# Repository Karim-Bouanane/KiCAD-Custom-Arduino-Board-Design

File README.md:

# **KiCAD-Custom-Arduino-Board-Design**

## **What is expected from this project ?**

This project goal was to touch the fundamental basis, from design to fabrication process of the PCB board. That's why I decided to build my own custom Arduino Nano Board from scratch using the KiCAD software which is totally free and offers many great tools. 
However due to my lack of some knowledge in electricity and the pressed time, I decided to give up some enhancements and postpone them when I finish my studies.

## **Subsystems**

## Voltage Regulator

I used the famous AMS117-3.3 voltage regulator known by its low cost and its availibity in the market. This IC can support a wide range of input voltage (4.0 up to 12V) and can deliver 3.3V with 1A output current capability. Its maximum drop out voltage can reach 1.3V.

The placement and values of capacitors were used from the datasheet. In addition I've added the Power On LED to lighten up when power is available.

## Oscillator

Ceramic and crystal oscillators are the main clock source and each has many types. The choice was mainly based on the frequency accuracy which provide each of them. Crystal Oscillator provides much more accurate output, of about 30 to 50ppm (part per million), than the Ceramic resonator which has +-1% of accuracy. The one I used for the atmega328 has a tolerance of 20ppm with a frequency of 16Mhz. The below circuit schema was made following the indication of datasheet.

## RESET pin

The reset pin is active low, so it needs a pull up resistor and I've added a switch button to put microcontroller in reset state manually in order to program it.

## Connectors

They are the interface we use to access the pins of the ATMEGA328P. The through whole connectors I used are the same as the ones on the Arduino Nano, they come ina single vertical row of 15 connectors with a size of 2.5mm. 

## UART pins

In order to observe any ongoing communication in the UART pins (RX, TX), I put two LEDS with a high resistance value.

## ICSP Interface

ICSP stands for In Circuit Serial Programming, which represents one of the several methods available for programming Arduino boards. Ordinarily, an Arduino bootloader program is used to program an Arduino board, but if the bootloader is missing or damaged, ICSP can be used instead. The ICSP uses pins of the SPI interface which are MISO, MOSI, SCK. 

## ATMEGA328P

### I2C pull up resistors

I2C peripheral uses open-drain pins so all they can do is assert the lines low, and pullup resistors pull the line high when it is not driven low. Also the pull-ups can be different values for different I2C speeds so they have to be external for that flexibility. I choosed the same value as like the ones used in Arduino Nano.

### AVCC low pass filter

So as to gain more accuracy in analogic operations, the data sheet for the ATMEGA328 chip says that AVCC should be connected externally to VCC via a low-pass filter if low noise is important to our application.

### User LED

This LED is attached to pin 13 and is built in most of the boards. It's not used by microcontroller but is there for the user to control. 

## **Whole Schemtaic**

## **3D front view**

## **3D back view**

## **References :**

Very informative references that I used:

- The official open source schematic published by arduino.cc

- This amazing website which thought me almost everything about every subsystem used in arduino with great explanation : https://rheingoldheavy.com/arduino-from-scratch-series/

- This is a concise playlist for using KiCAD software made by the incredible teacher Shawn Hymel which has a fun and attractive style of teaching : https://www.youtube.com/watch?v=vaCVh2SAZY4&list=PL3bNyZYHcRSUhUXUt51W6nKvxx2ORvUQB

- My selection of components was based on this list of parts that offer JLCPCB manufacturer:  https://jlcpcb.com/parts

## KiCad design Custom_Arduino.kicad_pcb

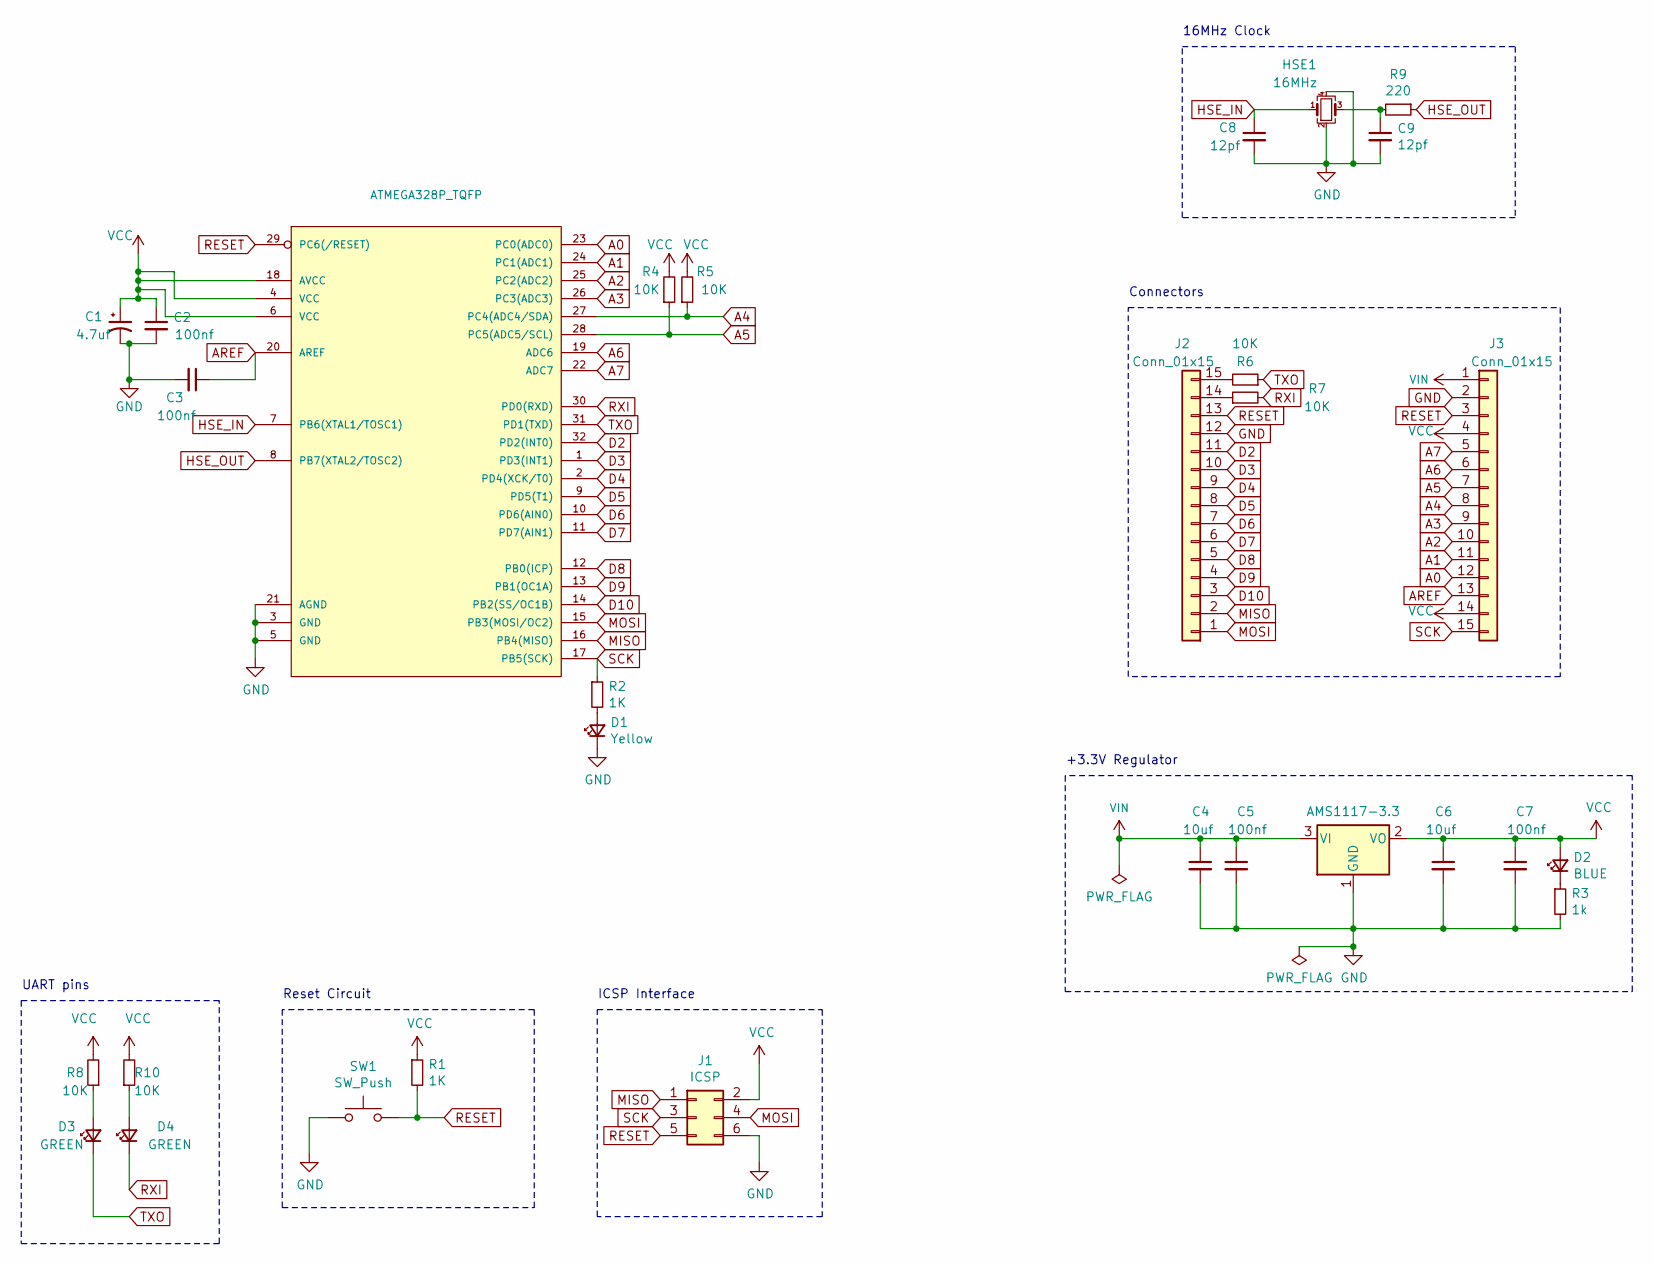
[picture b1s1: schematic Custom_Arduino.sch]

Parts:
C1: 4.7uf; C_0402_1005Metric
C2, C3, C5, C7: 100nf; C_0402_1005Metric
C4, C6: 10uf; C_0402_1005Metric
C8, C9: 12pf; C_0402_1005Metric
D1: Yellow; LED_0603_1608Metric
D2: BLUE; LED_0603_1608Metric
D3, D4: GREEN; LED_0603_1608Metric
HSE1: 16MHz; Crystal_SMD_3225-4Pin_3.2x2.5mm
J1: ICSP; PinHeader_2x03_P2.54mm_Vertical
J2, J3: Conn_01x15; PinHeader_1x15_P2.54mm_Vertical
R1, R2: 1K; R_0603_1608Metric
R3: 1k; R_0603_1608Metric
R4, R5, R6, R7, R8, R10: 10K; R_0603_1608Metric
R9: 220; R_0603_1608Metric
SW1: SW_Push; TACTILE_SWITCH_SMD_5.2MM
U1: ATMEGA328P_TQFP; TQFP32-08
U2: AMS1117-3.3; SOT-223-3_TabPin2

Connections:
A0: J3.12, U1.23 (PC0(ADC0))
A1: J3.11, U1.24 (PC1(ADC1))
A2: J3.10, U1.25 (PC2(ADC2))
A3: J3.9, U1.26 (PC3(ADC3))
A4: J3.8, R5.1, U1.27 (PC4(ADC4/SDA))
A5: J3.7, R4.1, U1.28 (PC5(ADC5/SCL))
A6: J3.6, U1.19 (ADC6)
A7: J3.5, U1.22 (ADC7)
AREF: C3.1, J3.13, U1.20 (AREF)
D2: J2.11, U1.32 (PD2(INT0))
D3: J2.10, U1.1 (PD3(INT1))
D4: J2.9, U1.2 (PD4(XCK/T0))
D5: J2.8, U1.9 (PD5(T1))
D6: J2.7, U1.10 (PD6(AIN0))
D7: J2.6, U1.11 (PD7(AIN1))
D8: J2.5, U1.12 (PB0(ICP))
D9: J2.4, U1.13 (PB1(OC1A))
D10: J2.3, U1.14 (PB2(SS/OC1B))
GND: C1.2, C2.2, C3.2, C4.2, C5.2, C6.2, C7.2, C8.2, C9.2, D1.1 (K), HSE1.2, HSE1.4, J1.6, J2.12, J3.2, R3.2, SW1.1, U1.3 (GND), U1.5 (GND), U1.21 (AGND), U2.1 (GND)
HSE_IN: C8.1, HSE1.1, U1.7 (PB6(XTAL1/TOSC1))
HSE_OUT: R9.1, U1.8 (PB7(XTAL2/TOSC2))
MISO: J1.1, J2.2, U1.16 (PB4(MISO))
MOSI: J1.4, J2.1, U1.15 (PB3(MOSI/OC2))
unnamed: C9.1, HSE1.3, R9.2
unnamed: D1.2 (A), R2.2
unnamed: D2.1 (K), R3.1
unnamed: D3.2 (A), R8.1
unnamed: D4.2 (A), R10.1
unnamed: J2.14, R7.1
unnamed: J2.15, R6.2
RESET: J1.5, J2.13, J3.3, R1.2, SW1.2, U1.29 (PC6(/RESET))
RXI: D4.1 (K), R7.2, U1.30 (PD0(RXD))
SCK: J1.3, J3.15, R2.1, U1.17 (PB5(SCK))
TXO: D3.1 (K), R6.1, U1.31 (PD1(TXD))
VCC: C1.1, C2.1, C6.1, C7.1, D2.2 (A), J1.2, J3.4, J3.14, R1.1, R4.2, R5.2, R8.2, R10.2, U1.4 (VCC), U1.6 (VCC), U1.18 (AVCC), U2.2 (VO)
VIN: C4.1, C5.1, J3.1, U2.3 (VI)

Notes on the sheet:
UART pins
ICSP Interface
Reset Circuit
Connectors
16MHz Clock
+3.3V Regulator

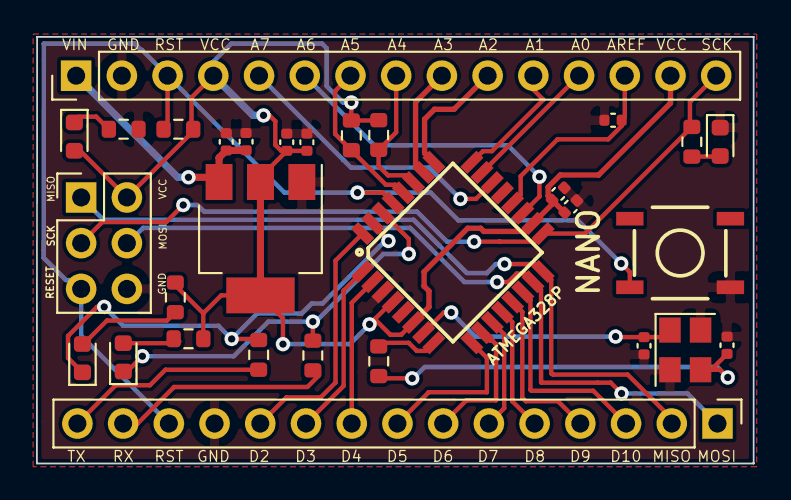
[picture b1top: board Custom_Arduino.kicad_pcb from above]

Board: 2 copper layers, 39.8 x 23.7 mm, 30 parts (0 on the bottom side), 36 nets.

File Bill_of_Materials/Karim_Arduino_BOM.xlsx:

Designator | Quantity | Value | Footprint | LCSC Part #
C1 | 1 | 4.7uf | Capacitor_SMD:C_0402_1005Metric | C23733
C2, C3, C5, C7 | 4 | 100nf | Capacitor_SMD:C_0402_1005Metric | C1525
C4, C6 | 2 | 10uf | Capacitor_SMD:C_0402_1005Metric | C15525
C8, C9 | 2 | 12pf | Capacitor_SMD:C_0402_1005Metric | C1547
D1 | 1 | Yellow | LED_SMD:LED_0603_1608Metric | C72038
D2 | 1 | BLUE | LED_SMD:LED_0603_1608Metric | C72041
D3, D4 | 2 | GREEN | LED_SMD:LED_0603_1608Metric | C72043
HSE1 | 1 | 16MHz | Crystal:Crystal_SMD_3225-4Pin_3.2x2.5mm | C13738
R1, R2 | 2 | 1K | Resistor_SMD:R_0603_1608Metric | C21190
R3 | 1 | 1k | Resistor_SMD:R_0603_1608Metric | C21190
R4, R5, R6, R7, R8, R10 | 6 | 10K | Resistor_SMD:R_0603_1608Metric | C25804
R9 | 1 | 220 | Resistor_SMD:R_0603_1608Metric | C22962
SW1 | 1 | SW_Push | Switches:TACTILE_SWITCH_SMD_5.2MM | C318887
U1 | 1 | ATMEGA328P_TQFP | Silicon-Standard:TQFP32-08 | C14877
U2 | 1 | AMS1117-3.3 | Package_TO_SOT_SMD:SOT-223-3_TabPin2 | C6186

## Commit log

2020-11-18 Fix ERC Issues
    -Power Flag
    -Output pin of voltage regulator was connected to bidirectional pin of the micro controller.
2020-11-19 Placing components on PCB
2020-11-19 Routing components
2020-11-19 Generate Gerber and Footprints files
2020-11-19 Completing Bill of Materials
2020-11-20 Update Footprints positions
2021-09-22 Update README and organize files
